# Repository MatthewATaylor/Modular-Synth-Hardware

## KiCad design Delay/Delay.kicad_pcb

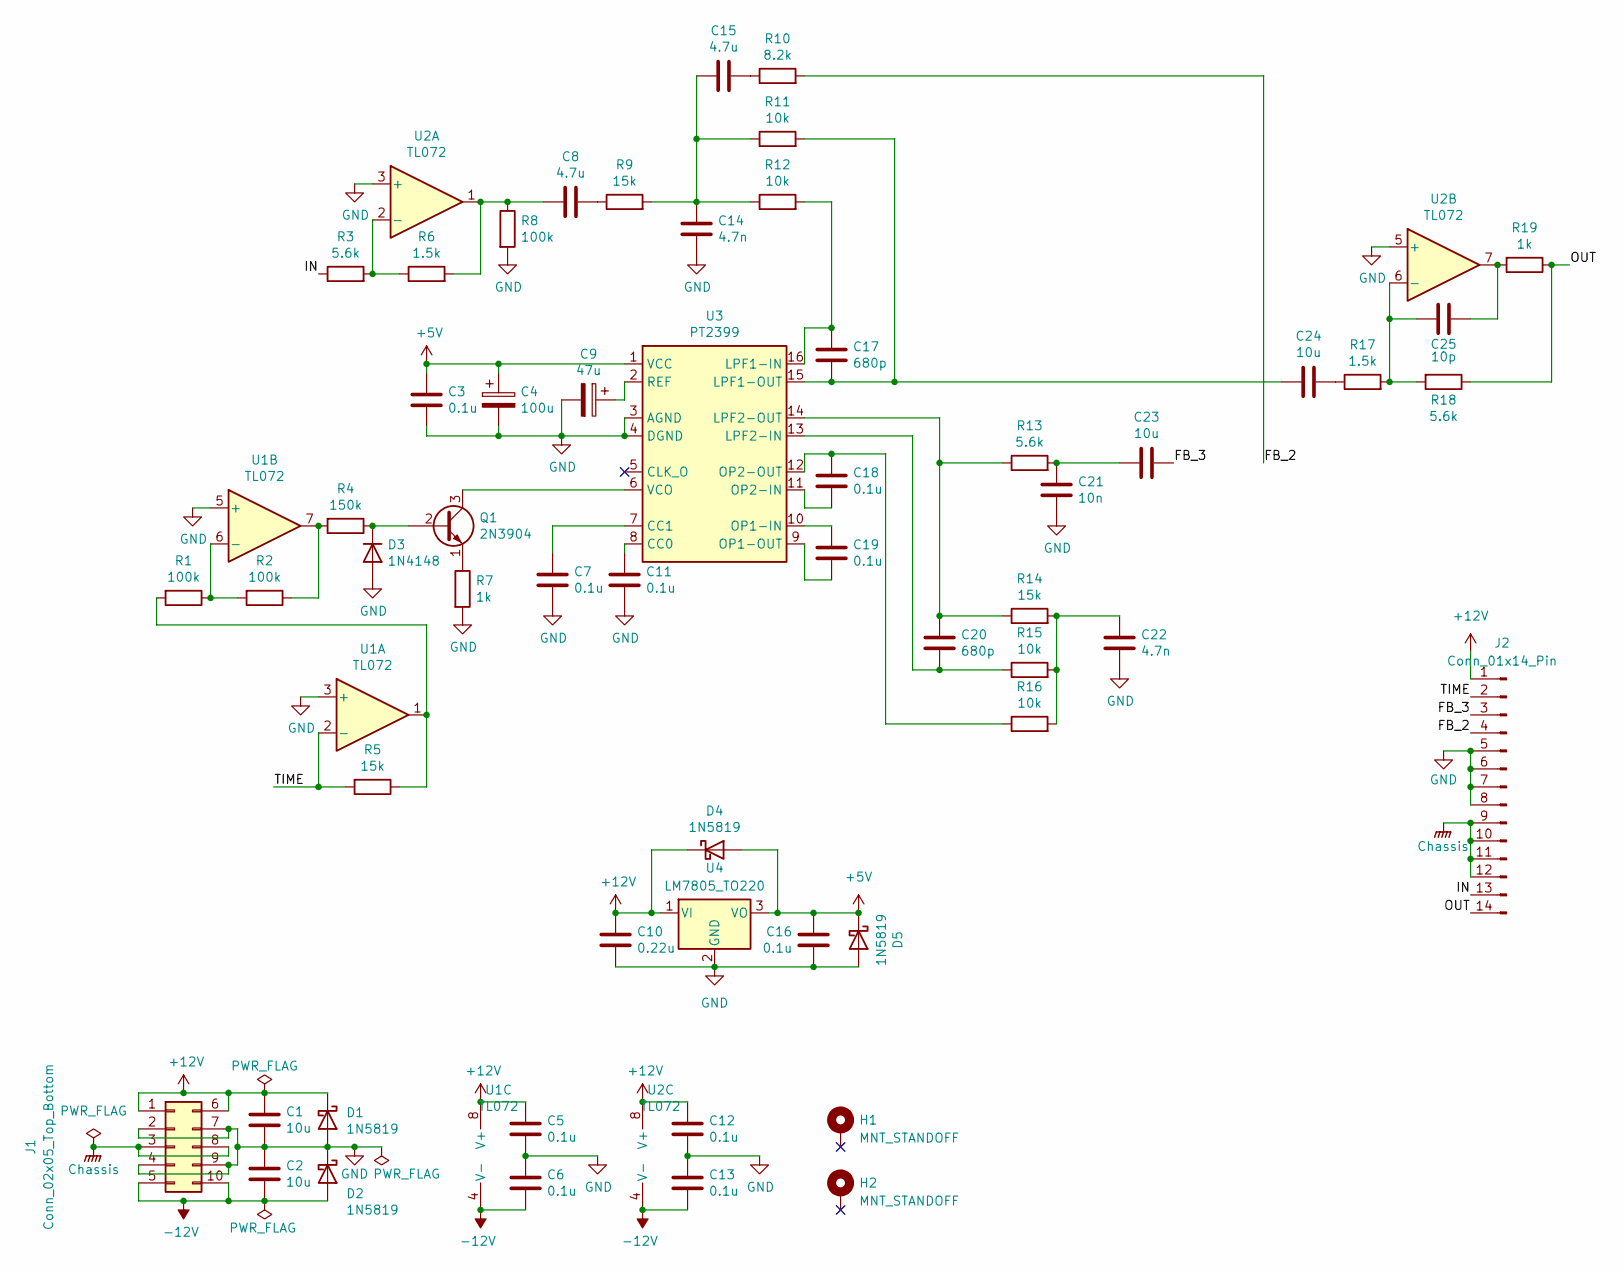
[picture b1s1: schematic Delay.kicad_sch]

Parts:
C1, C2, C23, C24: 10u; C_Disc_D5.5mm_W4.0mm_P2.50mm
C3, C5, C6, C7, C11, C12, C13, C16, C18, C19: 0.1u; C_Disc_D5.5mm_W2.5mm_P2.50mm
C4: 100u; CP_Radial_D6.3mm_P2.50mm
C8, C15: 4.7u; C_Disc_D3.8mm_W2.6mm_P2.50mm
C9: 47u; CP_Radial_D5.0mm_P2.50mm
C10: 0.22u; C_Disc_D5.5mm_W2.5mm_P2.50mm
C14, C22: 4.7n; C_Disc_D5.5mm_W2.5mm_P2.50mm
C17, C20: 680p; C_Disc_D5.5mm_W2.5mm_P2.50mm
C21: 10n; C_Disc_D5.5mm_W2.5mm_P2.50mm
C25: 10p; C_Disc_D5.5mm_W2.5mm_P2.50mm
D1, D2, D4, D5: 1N5819; D_DO-41_SOD81_P10.16mm_Horizontal
D3: 1N4148; D_DO-35_SOD27_P7.62mm_Horizontal
H1, H2: MNT_STANDOFF; MountingHole_Pitch7.5mm_Drill3.4mm
J1: Conn_02x05_Top_Bottom; Molex_Mini-Fit_Jr_5566-10A_2x05_P4.20mm_Vertical
J2: Conn_01x14_Pin; PinHeader_1x14_P2.54mm_Vertical
Q1: 2N3904; TO-92_HandSolder
R1, R2, R8: 100k; R_Axial_DIN0207_L6.3mm_D2.5mm_P7.62mm_Horizontal
R3, R13, R18: 5.6k; R_Axial_DIN0207_L6.3mm_D2.5mm_P7.62mm_Horizontal
R4: 150k; R_Axial_DIN0207_L6.3mm_D2.5mm_P7.62mm_Horizontal
R5, R9, R14: 15k; R_Axial_DIN0207_L6.3mm_D2.5mm_P7.62mm_Horizontal
R6, R17: 1.5k; R_Axial_DIN0207_L6.3mm_D2.5mm_P7.62mm_Horizontal
R7, R19: 1k; R_Axial_DIN0207_L6.3mm_D2.5mm_P7.62mm_Horizontal
R10: 8.2k; R_Axial_DIN0207_L6.3mm_D2.5mm_P7.62mm_Horizontal
R11, R12, R15, R16: 10k; R_Axial_DIN0207_L6.3mm_D2.5mm_P7.62mm_Horizontal
U1, U2: TL072; DIP-8_W7.62mm_Socket
U3: PT2399; DIP-16_W7.62mm
U4: LM7805_TO220; TO-220-3_Vertical

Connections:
+5V: C3.1, C4.1, C16.1, D4.2 (A), D5.1 (K), U3.1 (VCC), U4.3 (VO)
+12V: C1.1, C5.1, C10.1, C12.1, D1.1 (K), D4.1 (K), J1.1, J1.6, J2.1, U1.8 (V+), U2.8 (V+), U4.1 (VI)
-12V: C2.2, C6.2, C13.2, D2.2 (A), J1.5, J1.10, U1.4 (V-), U2.4 (V-)
/FB_2: J2.4, R10.2
/FB_3: C23.2, J2.3
/IN: J2.13, R3.1
/OUT: J2.14, R18.1, R19.1
/TIME: J2.2, R5.2, U1.2 (-)
Chassis: J1.3, J1.8, J2.9, J2.10, J2.11, J2.12
GND: C1.2, C2.1, C3.2, C4.2, C5.2, C6.1, C7.2, C9.2, C10.2, C11.2, C12.2, C13.1, C14.2, C16.2, C21.2, C22.2, D1.2 (A), D2.1 (K), D3.2 (A), D5.2 (A), J1.2, J1.4, J1.7, J1.9, J2.5, J2.6, J2.7, J2.8, R7.2, R8.2, U1.3 (+), U1.5 (+), U2.3 (+), U2.5 (+), U3.3 (AGND), U3.4 (DGND), U4.2 (GND)
unnamed: C8.1, R9.1
unnamed: C8.2, R6.2, R8.1, U2.1
unnamed: C14.1, C15.2, R9.2, R11.1, R12.1
unnamed: C15.1, R10.1
unnamed: C21.1, C23.1, R13.2
unnamed: C22.1, R14.2, R15.2, R16.2
unnamed: C24.2, R17.1
unnamed: C25.1, R19.2, U2.7
unnamed: D3.1 (K), Q1.2 (B), R4.1
unnamed: Q1.3 (C), U3.6 (VCO)
unnamed: Q1.1 (E), R7.1
unnamed: R1.2, R5.1, U1.1
unnamed: R2.1, R4.2, U1.7
unnamed: R1.1, R2.2, U1.6 (-)
unnamed: R3.2, R6.1, U2.2 (-)
unnamed: C25.2, R17.2, R18.2, U2.6 (-)
unnamed: C11.1, U3.8 (CC0)
unnamed: C7.1, U3.7 (CC1)
unnamed: C17.1, R12.2, U3.16 (LPF1-IN)
unnamed: C17.2, C24.1, R11.2, U3.15 (LPF1-OUT)
unnamed: C20.2, R15.1, U3.13 (LPF2-IN)
unnamed: C20.1, R13.1, R14.1, U3.14 (LPF2-OUT)
unnamed: C19.1, U3.10 (OP1-IN)
unnamed: C19.2, U3.9 (OP1-OUT)
unnamed: C18.2, U3.11 (OP2-IN)
unnamed: C18.1, R16.1, U3.12 (OP2-OUT)
unnamed: C9.1, U3.2 (REF)

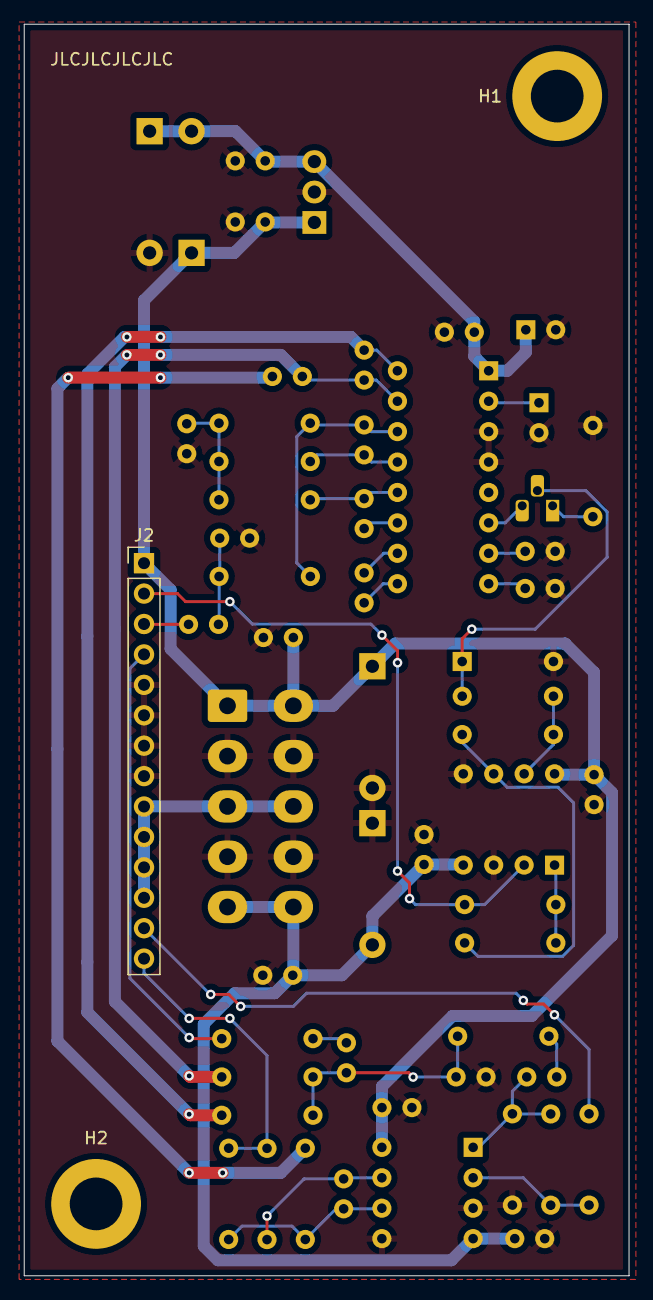
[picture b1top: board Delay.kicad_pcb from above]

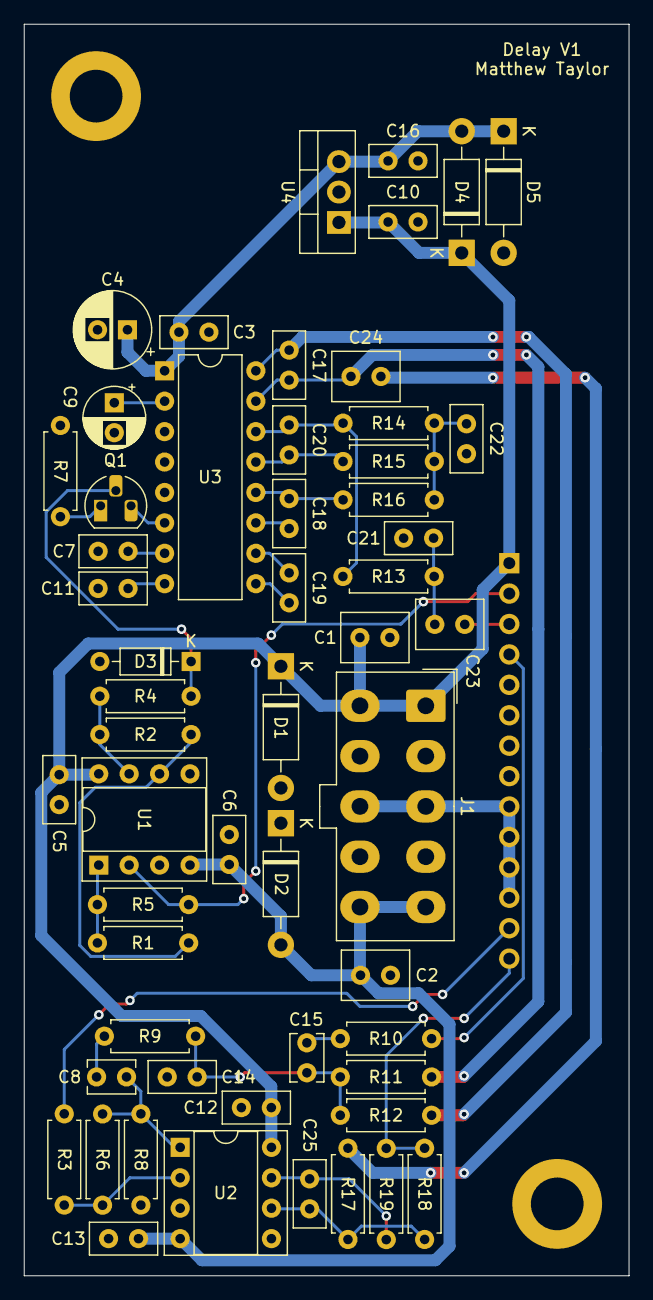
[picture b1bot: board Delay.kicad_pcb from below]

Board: 2 copper layers, 50.5 x 104.5 mm, 58 parts (55 on the bottom side), 37 nets.

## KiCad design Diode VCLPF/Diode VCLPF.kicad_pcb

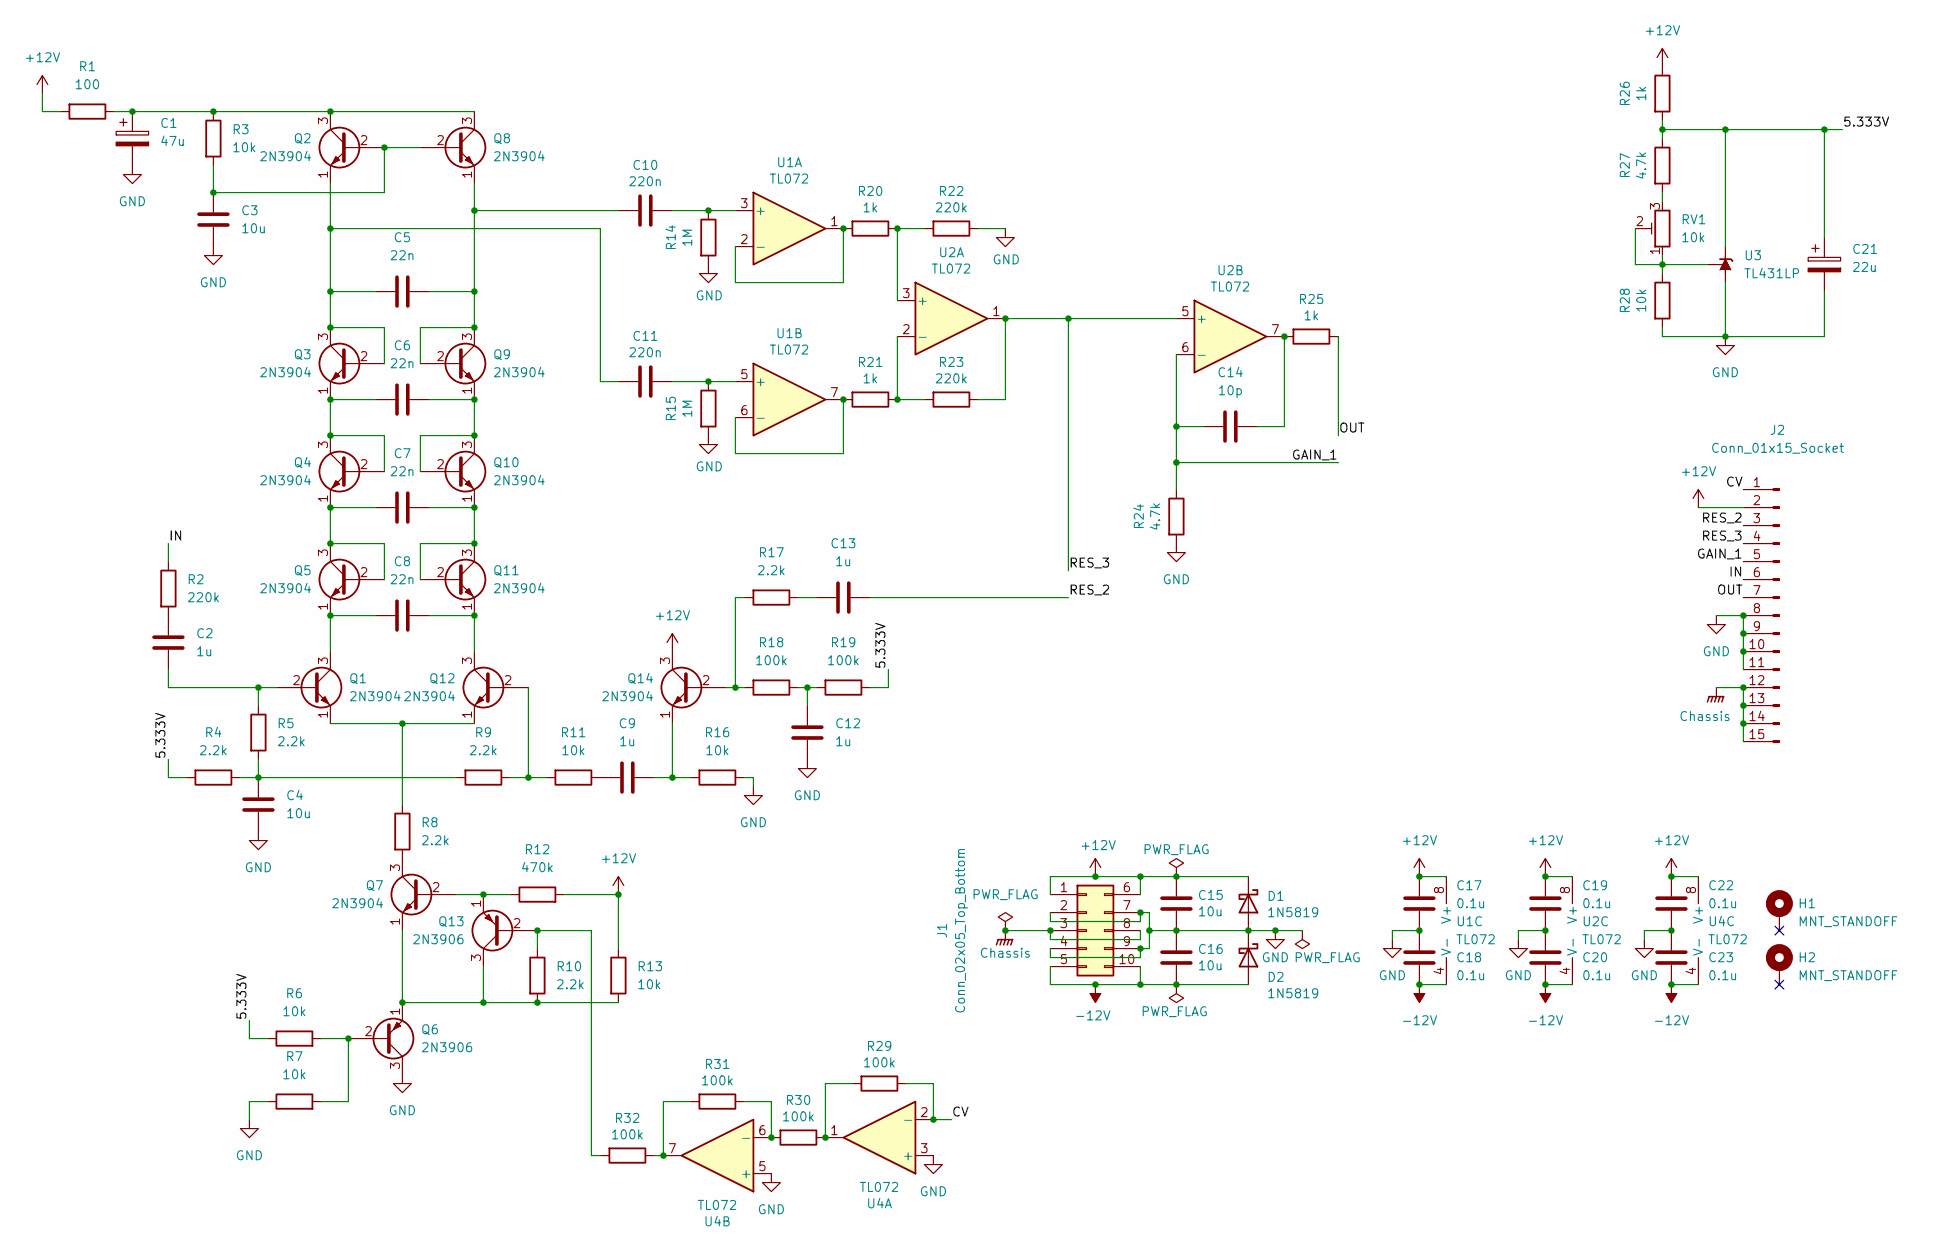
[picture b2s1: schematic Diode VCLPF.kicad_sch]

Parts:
C1: 47u; CP_Radial_D5.0mm_P2.50mm
C2, C9, C12, C13: 1u; C_Disc_D5.5mm_W4.0mm_P2.50mm
C3, C4, C15, C16: 10u; C_Disc_D5.5mm_W4.0mm_P2.50mm
C5, C6, C7, C8: 22n; C_Disc_D5.5mm_W2.5mm_P2.50mm
C10, C11: 220n; C_Disc_D5.5mm_W2.5mm_P2.50mm
C14: 10p; C_Disc_D5.5mm_W2.5mm_P2.50mm
C17, C18, C19, C20, C22, C23: 0.1u; C_Disc_D5.5mm_W2.5mm_P2.50mm
C21: 22u; CP_Radial_D5.0mm_P2.50mm
D1, D2: 1N5819; D_DO-41_SOD81_P10.16mm_Horizontal
H1, H2: MNT_STANDOFF; MountingHole_Pitch7.5mm_Drill3.4mm
J1: Conn_02x05_Top_Bottom; Molex_Mini-Fit_Jr_5566-10A_2x05_P4.20mm_Vertical
J2: Conn_01x15_Socket; PinHeader_1x15_P2.54mm_Vertical
Q1, Q2, Q3, Q4, Q5, Q7, Q8, Q9, Q10, Q11, Q12, Q14: 2N3904; TO-92_HandSolder
Q6, Q13: 2N3906; TO-92_HandSolder
R1: 100; R_Axial_DIN0207_L6.3mm_D2.5mm_P7.62mm_Horizontal
R2, R22, R23: 220k; R_Axial_DIN0207_L6.3mm_D2.5mm_P7.62mm_Horizontal
R3, R6, R7, R11, R13, R16, R28: 10k; R_Axial_DIN0207_L6.3mm_D2.5mm_P7.62mm_Horizontal
R4, R5, R8, R9, R10, R17: 2.2k; R_Axial_DIN0207_L6.3mm_D2.5mm_P7.62mm_Horizontal
R12: 470k; R_Axial_DIN0207_L6.3mm_D2.5mm_P7.62mm_Horizontal
R14, R15: 1M; R_Axial_DIN0207_L6.3mm_D2.5mm_P7.62mm_Horizontal
R18, R19, R29, R30, R31, R32: 100k; R_Axial_DIN0207_L6.3mm_D2.5mm_P7.62mm_Horizontal
R20, R21, R25, R26: 1k; R_Axial_DIN0207_L6.3mm_D2.5mm_P7.62mm_Horizontal
R24, R27: 4.7k; R_Axial_DIN0207_L6.3mm_D2.5mm_P7.62mm_Horizontal
RV1: 10k; Potentiometer_Bourns_3296W_Vertical
U1, U2, U4: TL072; DIP-8_W7.62mm_Socket
U3: TL431LP; TO-92_HandSolder

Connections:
+12V: C15.1, C17.2, C19.2, C22.2, D1.1 (K), J1.1, J1.6, J2.2, Q14.3 (C), R1.2, R12.2, R13.1, R26.1, U1.8 (V+), U2.8 (V+), U4.8 (V+)
-12V: C16.2, C18.1, C20.1, C23.1, D2.2 (A), J1.5, J1.10, U1.4 (V-), U2.4 (V-), U4.4 (V-)
/5.333V: C21.1, R4.2, R6.1, R19.1, R26.2, R27.1, U3.3 (K)
/CV: J2.1, R29.1, U4.2 (-)
/GAIN_1: C14.1, J2.5, R24.1, U2.6 (-)
/IN: J2.6, R2.1
/OUT: J2.7, R25.1
/RES_2: C13.2, J2.3
/RES_3: J2.4, R23.1, U2.1, U2.5 (+)
Chassis: J1.3, J1.8, J2.12, J2.13, J2.14, J2.15
GND: C1.2, C3.2, C4.2, C12.2, C15.2, C16.1, C17.1, C18.2, C19.1, C20.2, C21.2, C22.1, C23.2, D1.2 (A), D2.1 (K), J1.2, J1.4, J1.7, J1.9, J2.8, J2.9, J2.10, J2.11, Q6.3 (C), R7.1, R14.2, R15.2, R16.1, R22.1, R24.2, R28.2, U3.2 (A), U4.3 (+), U4.5 (+)
unnamed: C2.1, R2.2
unnamed: C4.1, R4.1, R5.2, R9.2
unnamed: C9.1, R11.1
unnamed: C12.1, R18.1, R19.2
unnamed: C13.1, R17.1
unnamed: C14.2, R25.2, U2.7
unnamed: C2.2, Q1.2 (B), R5.1
unnamed: C8.1, Q1.3 (C), Q5.1 (E)
unnamed: Q1.1 (E), Q12.1 (E), R8.1
unnamed: C3.1, Q2.2 (B), Q8.2 (B), R3.2
unnamed: C1.1, Q2.3 (C), Q8.3 (C), R1.1, R3.1
unnamed: C5.1, C11.1, Q2.1 (E), Q3.2 (B), Q3.3 (C)
unnamed: C6.1, Q3.1 (E), Q4.2 (B), Q4.3 (C)
unnamed: C7.1, Q4.1 (E), Q5.2 (B), Q5.3 (C)
unnamed: Q6.2 (B), R6.2, R7.2
unnamed: Q7.3 (C), R8.2
unnamed: C5.2, C10.1, Q8.1 (E), Q9.2 (B), Q9.3 (C)
unnamed: C6.2, Q9.1 (E), Q10.2 (B), Q10.3 (C)
unnamed: C7.2, Q10.1 (E), Q11.2 (B), Q11.3 (C)
unnamed: C8.2, Q11.1 (E), Q12.3 (C)
unnamed: Q12.2 (B), R9.1, R11.2
unnamed: Q13.2 (B), R10.1, R32.2
unnamed: Q6.1 (E), Q7.1 (E), Q13.3 (C), R10.2, R13.2
unnamed: Q7.2 (B), Q13.1 (E), R12.1
unnamed: Q14.2 (B), R17.2, R18.2
unnamed: C9.2, Q14.1 (E), R16.2
unnamed: R27.2, RV1.3
unnamed: R29.2, R30.1, U4.1
unnamed: R31.2, R32.1, U4.7
unnamed: C10.2, R14.1, U1.3 (+)
unnamed: R20.2, U1.1, U1.2 (-)
unnamed: C11.2, R15.1, U1.5 (+)
unnamed: R21.2, U1.6 (-), U1.7
unnamed: R20.1, R22.2, U2.3 (+)
unnamed: R21.1, R23.2, U2.2 (-)
unnamed: R28.1, RV1.1, RV1.2, U3.1 (REF)
unnamed: R30.2, R31.1, U4.6 (-)

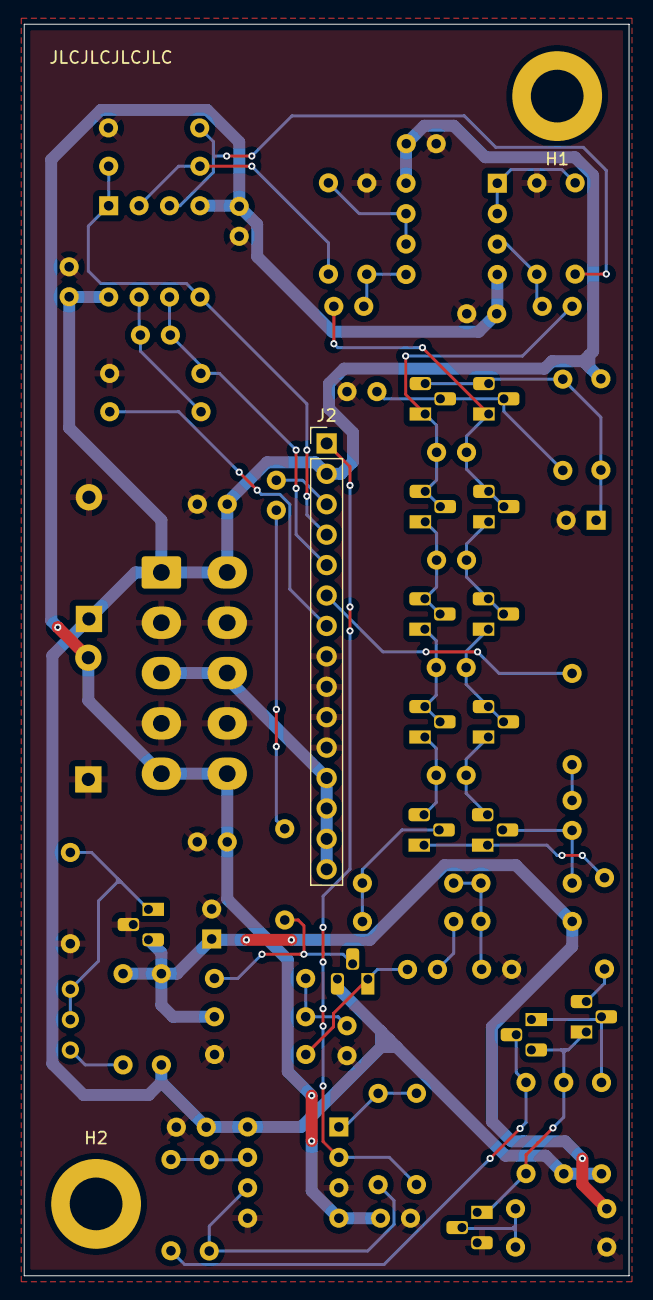
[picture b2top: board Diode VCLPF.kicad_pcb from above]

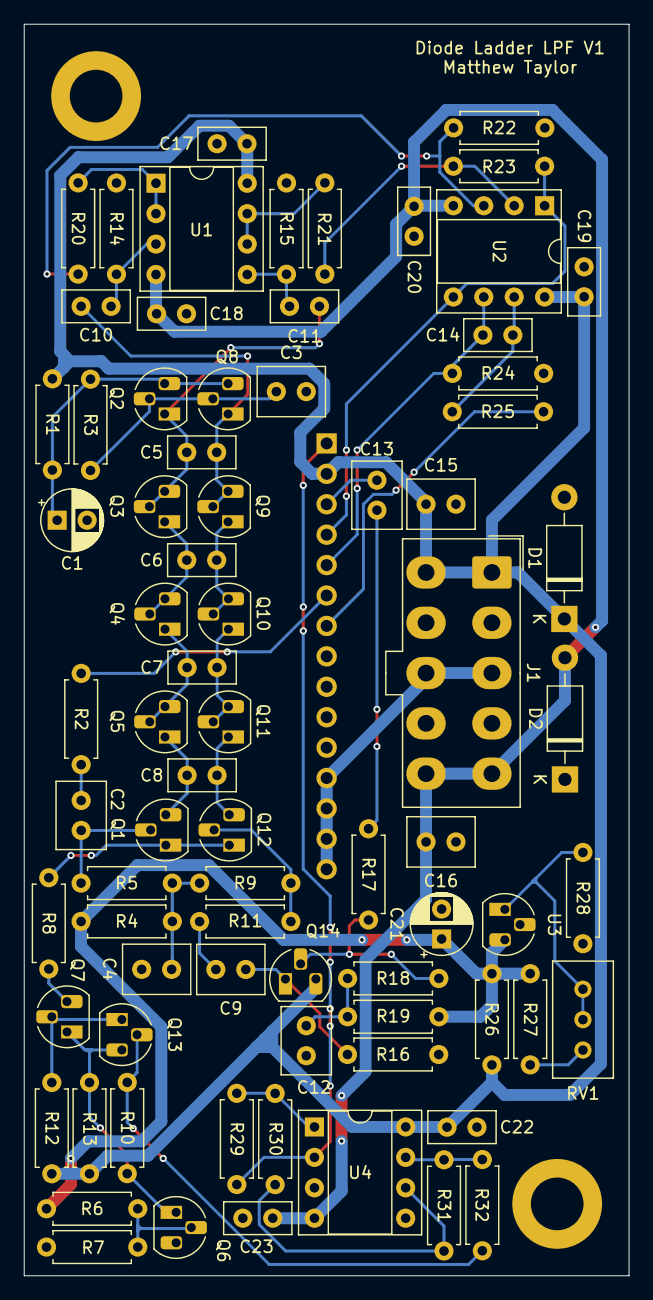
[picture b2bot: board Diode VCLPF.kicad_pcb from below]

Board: 2 copper layers, 50.5 x 104.5 mm, 80 parts (77 on the bottom side), 48 nets.

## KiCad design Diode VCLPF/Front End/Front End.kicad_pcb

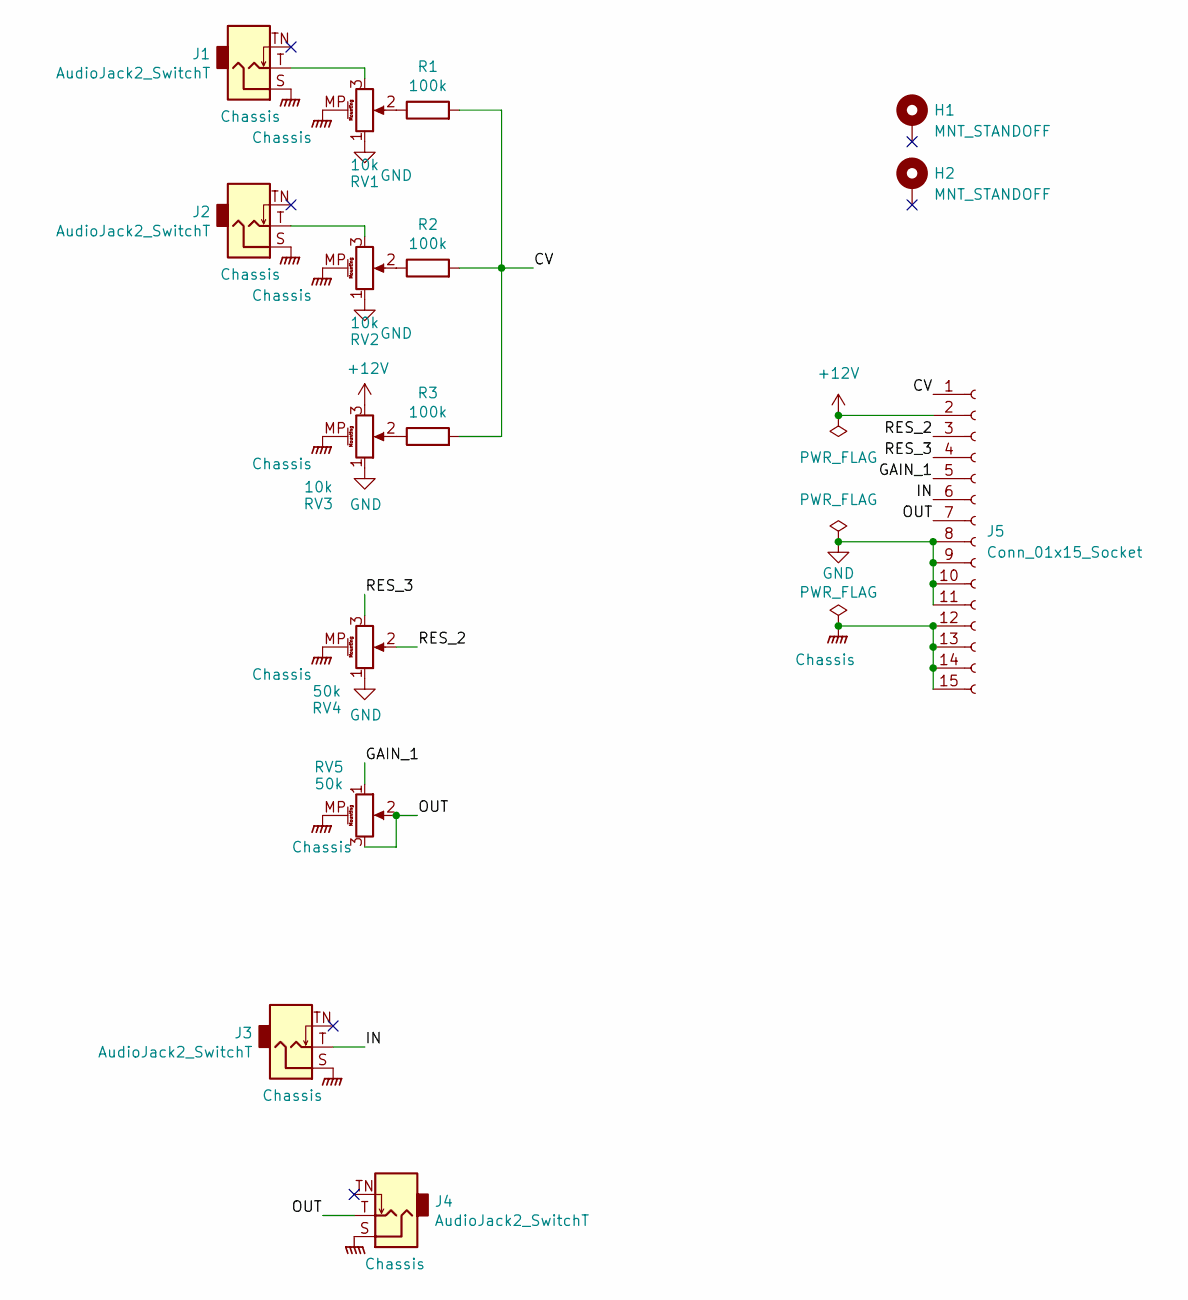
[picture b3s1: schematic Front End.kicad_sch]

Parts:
H1, H2: MNT_STANDOFF; MountingHole_Pitch7.5mm_Drill3.4mm
J1, J2, J3, J4: AudioJack2_SwitchT; Jack_3.5mm_QingPu_WQP-PJ398SM_Vertical_CircularHoles
J5: Conn_01x15_Socket; PinHeader_1x15_P2.54mm_Vertical
R1, R2, R3: 100k; R_Axial_DIN0207_L6.3mm_D2.5mm_P7.62mm_Horizontal
RV1, RV2, RV3: 10k; Potentiometer_Alpha_RD901F-40-00D_Single_Vertical_MP
RV4, RV5: 50k; Potentiometer_Alpha_RD901F-40-00D_Single_Vertical_MP

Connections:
+12V: J5.2, RV3.3
/CV: J5.1, R1.2, R2.2, R3.2
/GAIN_1: J5.5, RV5.1
/IN: J3.T, J5.6
/OUT: J4.T, J5.7, RV5.2, RV5.3
/RES_2: J5.3, RV4.2
/RES_3: J5.4, RV4.3
Chassis: J1.S, J2.S, J3.S, J4.S, J5.12, J5.13, J5.14, J5.15, RV1.MP (MountPin), RV2.MP (MountPin), RV3.MP (MountPin), RV4.MP (MountPin), RV5.MP (MountPin)
GND: J5.8, J5.9, J5.10, J5.11, RV1.1, RV2.1, RV3.1, RV4.1
unnamed: J1.T, RV1.3
unnamed: J2.T, RV2.3
unnamed: R1.1, RV1.2
unnamed: R2.1, RV2.2
unnamed: R3.1, RV3.2

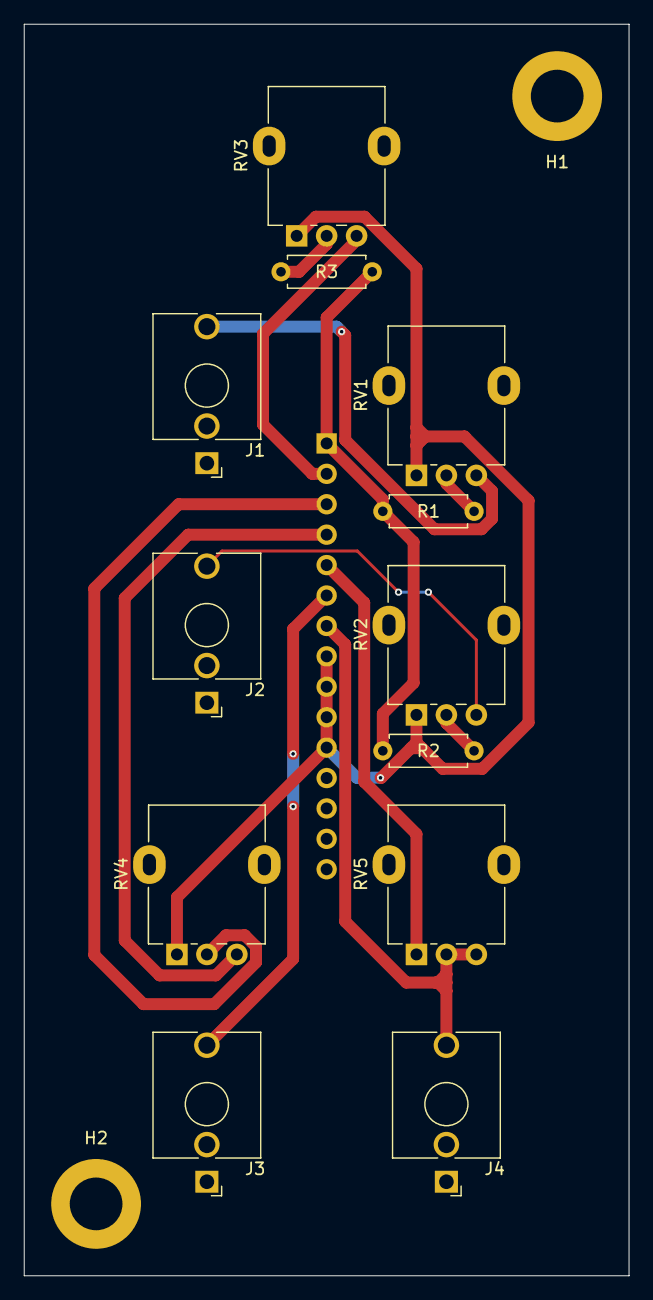
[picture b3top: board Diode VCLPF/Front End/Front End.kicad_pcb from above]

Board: 2 copper layers, 50.5 x 104.5 mm, 15 parts (1 on the bottom side), 14 nets.

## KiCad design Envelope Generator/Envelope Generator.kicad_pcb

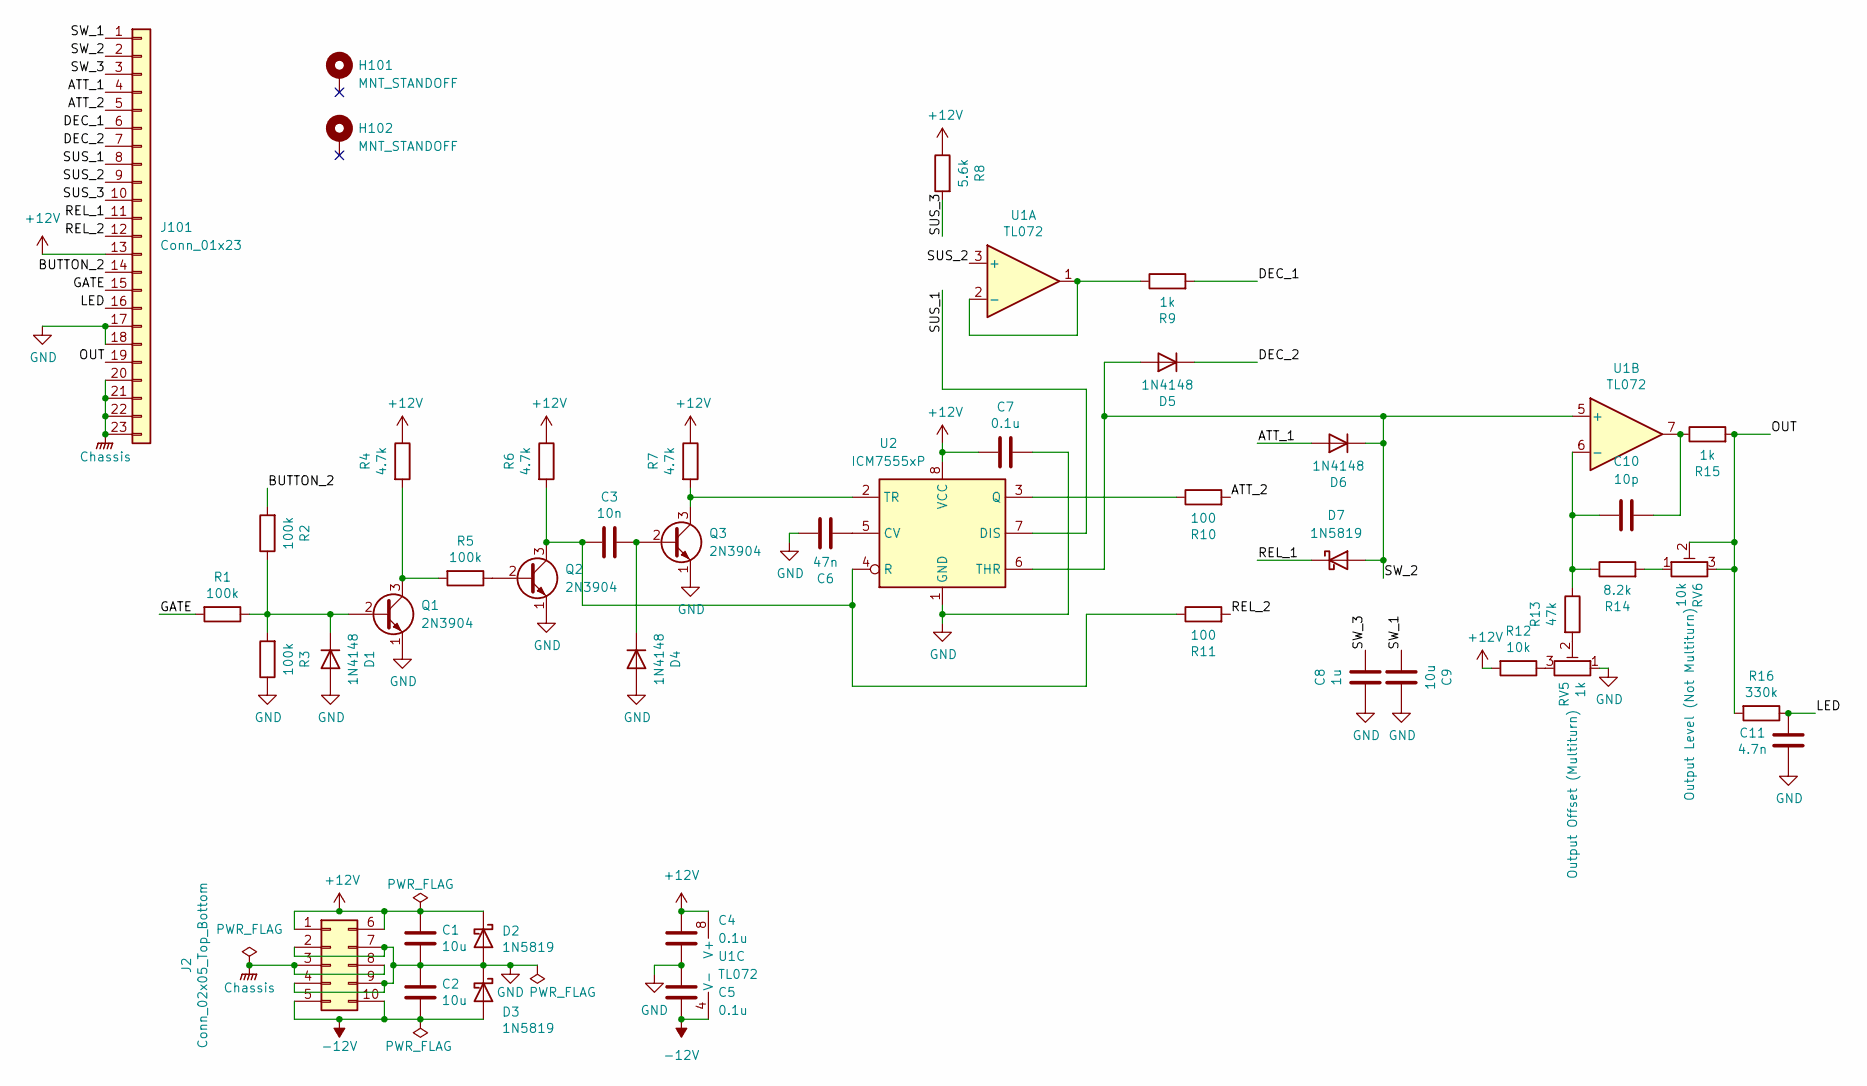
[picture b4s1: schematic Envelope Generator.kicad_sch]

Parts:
C1, C2, C9: 10u; C_Disc_D5.5mm_W4.0mm_P2.50mm
C3: 10n; C_Disc_D5.5mm_W2.5mm_P2.50mm
C4, C5, C7: 0.1u; C_Disc_D5.5mm_W2.5mm_P2.50mm
C6: 47n; C_Disc_D5.5mm_W2.5mm_P2.50mm
C8: 1u; C_Disc_D5.5mm_W4.0mm_P2.50mm
C10: 10p; C_Disc_D5.5mm_W2.5mm_P2.50mm
C11: 4.7n; C_Disc_D5.5mm_W2.5mm_P2.50mm
D1, D4, D5, D6: 1N4148; D_DO-35_SOD27_P7.62mm_Horizontal
D2, D3, D7: 1N5819; D_DO-41_SOD81_P10.16mm_Horizontal
H101, H102: MNT_STANDOFF; MountingHole_Pitch7.5mm_Drill3.4mm
J2: Conn_02x05_Top_Bottom; Molex_Mini-Fit_Jr_5566-10A_2x05_P4.20mm_Vertical
J101: Conn_01x23; PinHeader_1x23_P2.54mm_Vertical
Q1, Q2, Q3: 2N3904; TO-92_HandSolder
R1, R2, R3, R5: 100k; R_Axial_DIN0207_L6.3mm_D2.5mm_P7.62mm_Horizontal
R4, R6, R7: 4.7k; R_Axial_DIN0207_L6.3mm_D2.5mm_P7.62mm_Horizontal
R8: 5.6k; R_Axial_DIN0207_L6.3mm_D2.5mm_P7.62mm_Horizontal
R9, R15: 1k; R_Axial_DIN0207_L6.3mm_D2.5mm_P7.62mm_Horizontal
R10, R11: 100; R_Axial_DIN0207_L6.3mm_D2.5mm_P7.62mm_Horizontal
R12: 10k; R_Axial_DIN0207_L6.3mm_D2.5mm_P7.62mm_Horizontal
R13: 47k; R_Axial_DIN0207_L6.3mm_D2.5mm_P7.62mm_Horizontal
R14: 8.2k; R_Axial_DIN0207_L6.3mm_D2.5mm_P7.62mm_Horizontal
R16: 330k; R_Axial_DIN0207_L6.3mm_D2.5mm_P7.62mm_Horizontal
RV5: 1k; Potentiometer_Runtron_RM-065_Vertical
RV6: 10k; Potentiometer_Runtron_RM-065_Vertical
U1: TL072; DIP-8_W7.62mm_Socket
U2: ICM7555xP; DIP-8_W7.62mm_Socket

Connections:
+12V: C1.1, C4.2, C7.1, D2.1 (K), J2.1, J2.6, J101.13, R4.1, R6.1, R7.1, R8.1, R12.2, U1.8 (V+), U2.8 (VCC)
-12V: C2.2, C5.1, D3.2 (A), J2.5, J2.10, U1.4 (V-)
/ATT_1: D6.2 (A), J101.4
/ATT_2: J101.5, R10.2
/BUTTON_2: J101.14, R2.2
/DEC_1: J101.6, R9.2
/DEC_2: D5.1 (K), J101.7
/GATE: J101.15, R1.2
/LED: C11.1, J101.16, R16.1
/OUT: J101.19, R15.2, R16.2, RV6.2, RV6.3
/REL_1: D7.1 (K), J101.11
/REL_2: J101.12, R11.2
/SUS_1: J101.8, U2.7 (DIS)
/SUS_2: J101.9, U1.3 (+)
/SUS_3: J101.10, R8.2
/SW_1: C9.1, J101.1
/SW_2: D5.2 (A), D6.1 (K), D7.2 (A), J101.2, U1.5 (+), U2.6 (THR)
/SW_3: C8.2, J101.3
Chassis: J2.3, J2.8, J101.20, J101.21, J101.22, J101.23
GND: C1.2, C2.1, C4.1, C5.2, C6.2, C7.2, C8.1, C9.2, C11.2, D1.2 (A), D2.2 (A), D3.1 (K), D4.2 (A), J2.2, J2.4, J2.7, J2.9, J101.17, J101.18, Q1.1 (E), Q2.1 (E), Q3.1 (E), R3.1, RV5.1, U2.1 (GND)
unnamed: C10.1, R15.1, U1.7
unnamed: D1.1 (K), Q1.2 (B), R1.1, R2.1, R3.2
unnamed: C3.2, D4.1 (K), Q3.2 (B)
unnamed: Q1.3 (C), R4.2, R5.2
unnamed: Q2.2 (B), R5.1
unnamed: C3.1, Q2.3 (C), R6.2, R11.1, U2.4 (R)
unnamed: Q3.3 (C), R7.2, U2.2 (TR)
unnamed: R12.1, RV5.3
unnamed: R13.2, RV5.2
unnamed: R14.2, RV6.1
unnamed: R9.1, U1.1, U1.2 (-)
unnamed: C10.2, R13.1, R14.1, U1.6 (-)
unnamed: C6.1, U2.5 (CV)
unnamed: R10.1, U2.3 (Q)

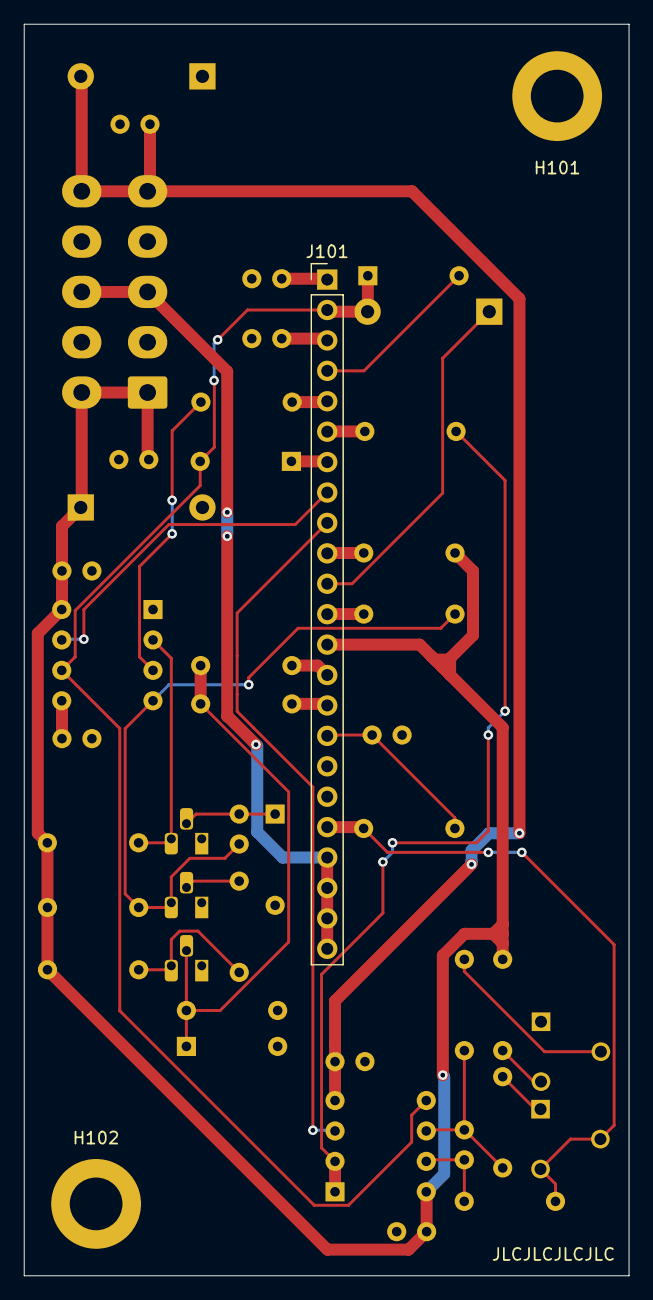
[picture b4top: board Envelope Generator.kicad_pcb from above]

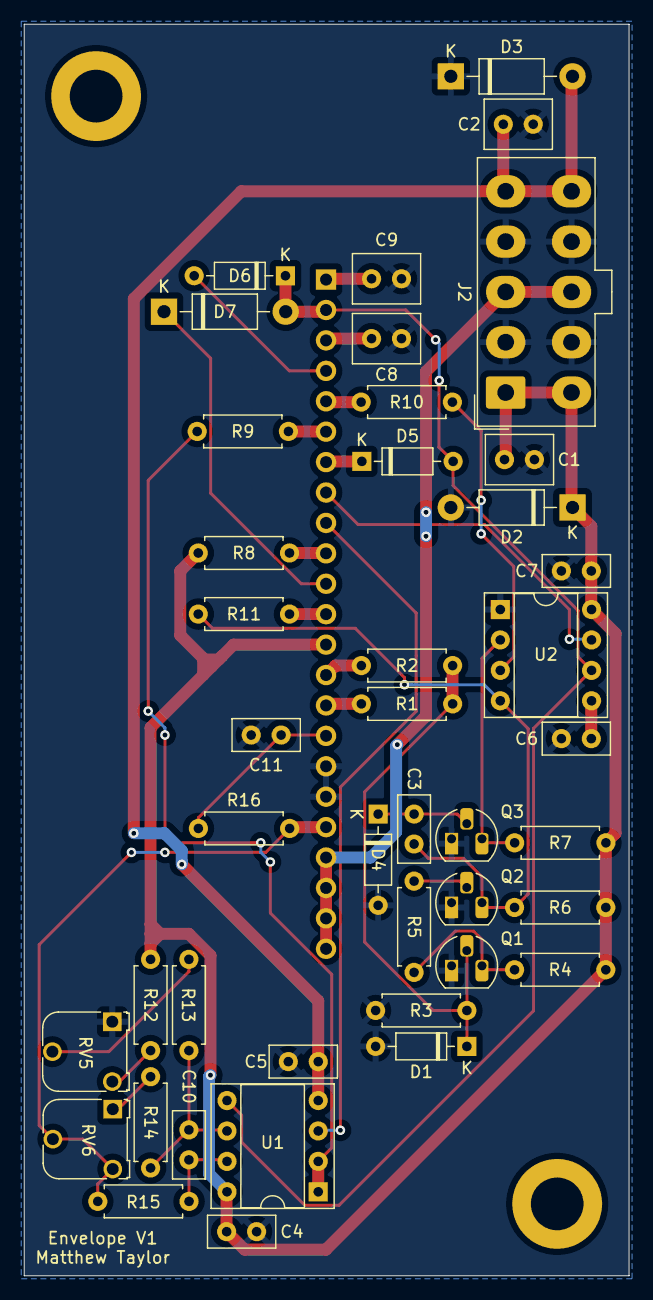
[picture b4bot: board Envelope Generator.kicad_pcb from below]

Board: 2 copper layers, 50.5 x 104.5 mm, 45 parts (42 on the bottom side), 34 nets.
